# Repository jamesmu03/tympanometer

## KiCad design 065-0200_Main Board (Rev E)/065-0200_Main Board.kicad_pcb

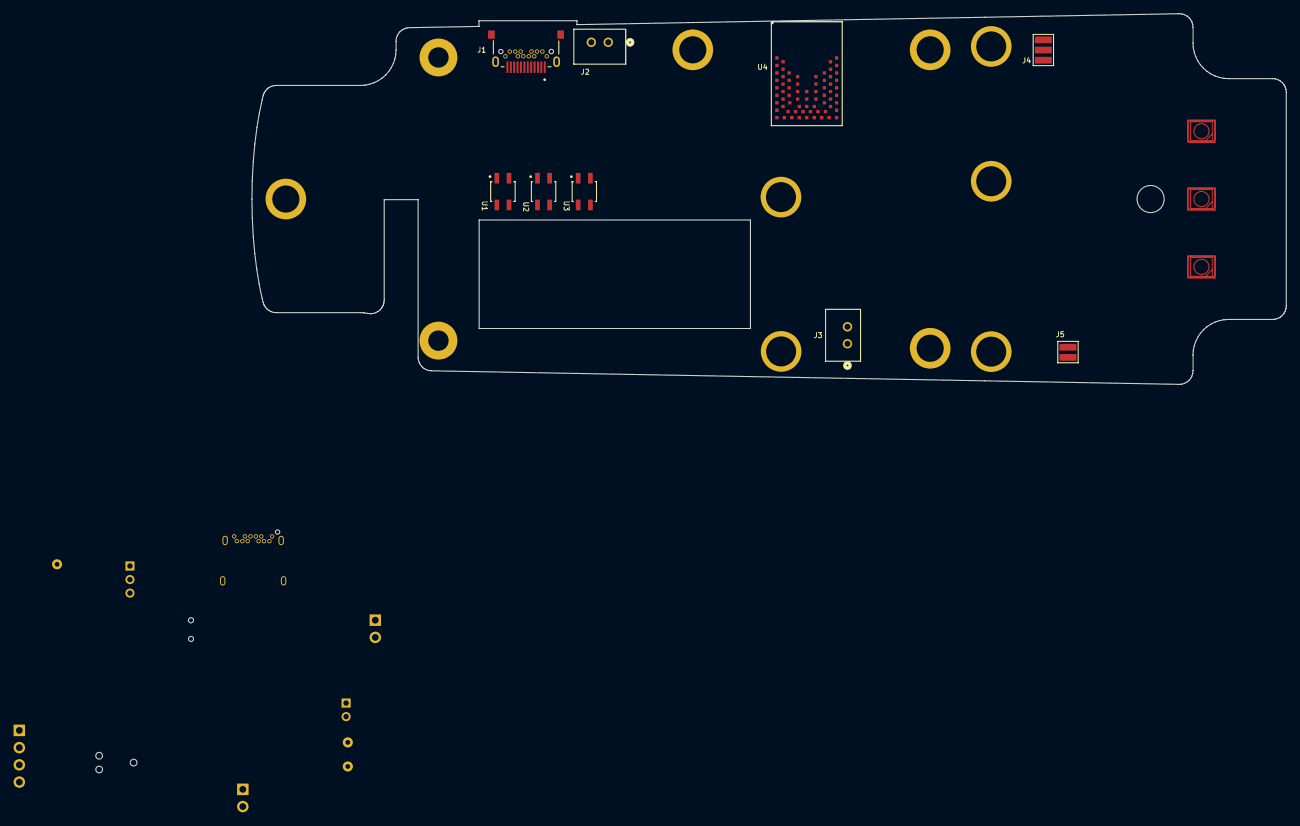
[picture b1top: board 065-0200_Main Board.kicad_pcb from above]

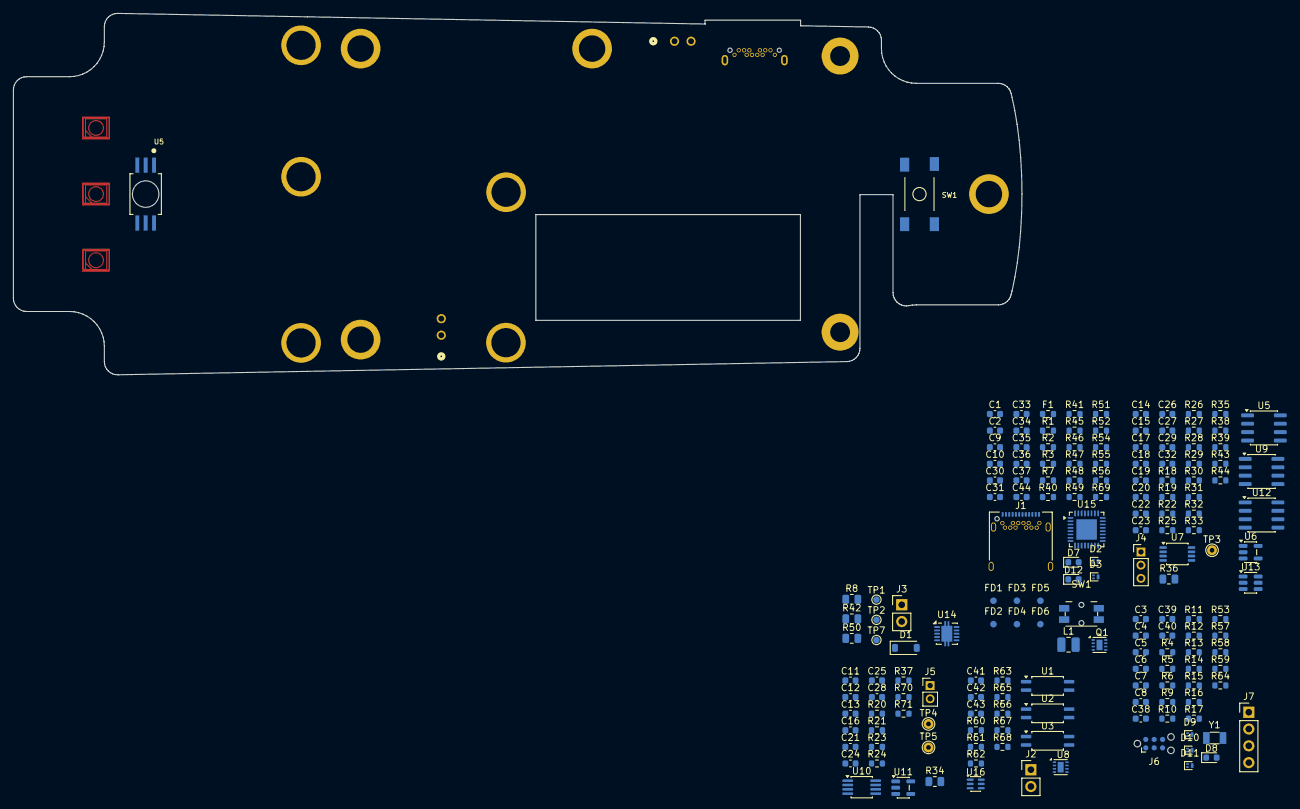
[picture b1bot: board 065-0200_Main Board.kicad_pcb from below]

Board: 2 copper layers, 152.5 x 54.6 mm, 188 parts (168 on the bottom side), 90 nets, no tracks yet.

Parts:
C1, C2, C3, C4, C5, C6, C7, C8, C9, C10, C11, C12, C13, C14, C15, C16, C17, C18, C19, C20, C21, C22, C23, C24, C25, C26, C27, C28, C29, C31, C32, C36, C37, C38, C39, C40, C41, C42, C43, C44: Cap_Ceramic; C_0603_1608Metric
C30, C33, C34: CL10A226MO7JZNC; C_0603_1608Metric
C35: C0603C102K5RACTU; C_0603_1608Metric
D1: ATV02W120B-HF; D_SOD-123
D2, D3, D9, D10, D11: D5V0H1B2LP-7B; SOT-883
D4, D5, D6: CLVBA-FKA-CAEDH8BBB7A363; LED_Cree-PLCC4_3.2x2.8mm_CCW
D7, D8, D12: APT1608ZGCK; LED_0603_1608Metric
F1: C2Q 2.5; R_0603_1608Metric
FD1, FD2, FD3, FD4, FD5, FD6: DNI; Fiducial_1mm_Mask2mm
J1: UJ32-C-H-G-H2-SMT-TR; CUI_UJ32-C-H-G-H2-SMT-TR
J1#2: UJ32-C-H-G-H2-SMT-TR; USB_C_Receptacle_Amphenol_12401548E4-2A
J2, J3: 0022035025; Molex_2P-2.50_22035025
J2#2, J3#2: 0022035025; PinHeader_1x02_P2.54mm_Vertical
J4: custom_3p_2mm; Custom_3p-2MM
J4#2: custom_3p_2mm; PinHeader_1x03_P2.00mm_Vertical
J5: custom_2p_2mm; Custom_2p-2MM
J5#2: custom_2p_2mm; PinHeader_1x02_P2.00mm_Vertical
J6: TC2030-CTX; Tag-Connect_TC2030-IDC-NL_2x03_P1.27mm_Vertical
J7: Conn_01x04_Pin; PinHeader_1x04_P2.54mm_Vertical
L1: CIGT252012LMR47MNE; L_1008_2520Metric
MH1, MH4, MH7, MH8: DNI; MH_M3_Pad
MH2, MH3, MH5, MH6, MH9, MH10, MH11: DNI; MH_M2.5_Pad
Q1: CSD25402Q3A; WSON-8-1EP_2x2mm_P0.5mm_EP0.9x1.6mm
R1, R2, R3, R4, R5, R6, R7, R9, R10, R11, R12, R13, R14, R15, R16, R17, R18, R19, R20, R21, R22, R23, R24, R25, R26, R27, R29, R30, R31, R32, R33, R35, R37, R38, R39, R40, R41, R43, R44, R45, R46, R47, R48, R49, R51, R52, R53, R54, R55, R56, R57, R58, R59, R60, R61, R62, R63, R64, R65, R66, R67, R68, R69, R70, R71: Resistor; R_0603_1608Metric
R8, R34, R36, R42, R50: Resistor; R_0805_2012Metric
R28: ERJ-3EKF6810V; R_0603_1608Metric
SW1: 3-1437565-0; Panasonic_EVQPUL_EVQPUC
SW1#2: 3-1437565-0; SW_TE_3-1437565-0
TP1, TP2, TP7: TP SMT Round 30mil; TestPoint_Pad_D1.0mm
TP3, TP4, TP5: TP TH Round 45 mil sqr, 25mil hole; TestPoint_THTPad_D1.5mm_Drill0.7mm
U1, U2, U3: QRE1113GR; SOIC180P460X187-4N
U1#2, U2#2, U3#2: QRE1113GR; SOIC-4_4.55x2.6mm_P1.27mm
U4: BM833
U5: 2SMPP03; 6SOP_2SMPP-03
U5#2: 2SMPP03; SOIC-8_3.9x4.9mm_P1.27mm
U6, U11: TLV313IDBVT; SOT-23-5
U7: INA326; TSSOP-8_3x3mm_P0.65mm
U8: DRV8837DSGR; WSON-8-1EP_2x2mm_P0.5mm_EP0.9x1.6mm
U9: LM334MX/NOPB; SOIC-8_3.9x4.9mm_P1.27mm
U10: LM4875MM/NOPB; MSOP-8_3x3mm_P0.65mm
U12: LM393DMR2G; SOIC-8_3.9x4.9mm_P1.27mm
U13: MAX9109EUT+T; SOT-23-6
U14: TPS63802DLAT; VSON-10-1EP_3x3mm_P0.5mm_EP1.65x2.4mm
U15: NPM1300-QEAA-R; QFN-32-1EP_5x5mm_P0.5mm_EP3.1x3.1mm
U16: 74LVC1G27GW,12; SOT-363_SC-70-6
Y1: 9HT10-32.768KBZF-T; Crystal_SMD_3215-2Pin_3.2x1.5mm

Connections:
+3V3: C7.2, C8.1, C14.1, C16.2, C20.1, C23.1, C24.2, C26.1, C27.2, C29.2, C32.2, C35.2, C39.1, C40.2, C41.2, C42.2, C43.2, J6.1 (VCC), J7.3, R4.2, R23.2, R29.2, R33.2, R35.1, R36.2, R42.2, R43.2, R53.2, R57.2, R58.2, R59.2, R62.2, R63.2, R65.2, R66.2, R67.2, R68.2, R69.2, U4.14, U4.28, U6.5 (+V), U7.7 (V+), U8.1 (VM), U8.8 (VCC), U9.4 (V+), U10.1 (VDD), U11.5 (+V), U12.8 (VCC), U13.6 (+V), U15.12 (VDDIO), U16.5 (VCC)
/Micro/BMD_RESET: C38.1, D9.2, J6.3 (nRESET), R59.1
/Micro/BMD_SWCLK: D10.2, J6.4 (SWCLK)
/Micro/BMD_SWDIO: D11.2, J6.2 (SWDIO)
/Micro/Back_Limit: R67.1, U1#2.3 (CT)
/Micro/Center_Limit: R65.1, U2#2.3 (CT)
/Micro/ENV_OUT: R19.2, TP3.1 (1_1), U6.1 (OUT)
/Micro/Front_Limit: R62.1, U3#2.3 (CT)
/Micro/MTR_DRV1: R61.2, U8.6 (IN1)
/Micro/MTR_DRV2: R60.2, U8.5 (IN2)
/Micro/MTR_SLEEP: R64.2, U16.3 (B)
/Micro/PRESSURE: C22.2, R31.2, U12.2 (INA-), U12.5 (INB+)
/Micro/Pressure_Error: U13.1 (OUT), U13.5 (LE), U16.6 (C)
/Micro/SCL: J7.2, R57.1, U15.14 (SCL)
/Micro/SDA: J7.1, R58.1, U15.13 (SDA)
/Micro/USB_D_N: D2.2, J1#2.A7 (DN1), J1#2.B7 (DN2)
/Micro/USB_D_P: D3.2, J1#2.A6 (DP1), J1#2.B6 (DP2)
Back_Limit: U1.3, U4.21
Center_Limit: U2.3, U4.10
Front_Limit: U3.3, U4.12
GND: C1.1, C2.1, C3.1, C4.1, C5.2, C6.1, C7.1, C8.2, C9.1, C10.1, C11.2, C12.2, C13.2, C14.2, C15.2, C16.1, C17.2, C19.2, C20.2, C22.1, C23.2, C24.1, C25.1, C26.2, C27.1, C28.2, C29.1, C30.1, C31.2, C32.1, C33.1, C34.1, C35.1, C36.1, C37.1, C38.2, C39.2, C40.1, C41.1, C42.1, C43.1, C44.1, C44.2, D1.1, D2.1, D3.1, D7.1 (K), D9.1, D10.1, D11.1, D12.1 (K), J1.A1, J1.A12, J1.B1, J1.B12, J1.SH1, J1.SH2, J1.SH3, J1.SH4, J1#2.A1 (GND), J1#2.A12 (GND), J1#2.B1 (GND), J1#2.B12 (GND), J1#2.SH (SHIELD), J3.2, J3#2.2, J4.1, J4#2.1, J6.5 (GND), J7.4, MH1.1, MH2.1, MH3.1, MH5.1, MH6.1, MH8.1, MH10.1, MH11.1, Q1.8 (G), R1.1, R2.1, R3.1, R5.1, R7.1, R18.1, R24.2, R26.1, R27.1, R39.1, R40.1, R44.1, R54.2, R55.2, R56.2, R60.1, R61.1, R64.1, R70.1, R71.1, SW1.1, SW1.2, SW1#2.1, SW1#2.2, U1.2, U1.4, U1#2.2 (C), U1#2.4 (ET), U2.2, U2.4, U2#2.2 (C), U2#2.4 (ET), U3.2, U3.4, U3#2.2 (C), U3#2.4 (ET), U4.1, U4.2, U4.3, U4.4, U4.5, U4.13, U4.15, U4.18, U4.19, U4.30, U4.45, U5.3, U5#2.3 (GND), U6.2 (-V), U7.4 (V-), U8.4 (GND), U8.9 (Therm), U10.6 (GND), U11.2 (-V), U12.4 (GND), U13.2 (GND), U14.2 (MODE), U14.3 (AGND), U14.8 (GND), U15.2 (PVSS1), U15.6 (PVSS2), U15.15 (SHPHLD), U15.16 (VSET2), U15.17 (VSET1), U15.28 (LSIN1/__VINLDO1), U15.29 (LSOUT1/__VOUTLDO1), U15.30 (LSIN2/__VINLDO2), U15.31 (LSOUT2/_VOUTLDO2), U15.33 (AVSS__EXT_PAD), U16.2 (GND)
unnamed: C11.1, C12.1, C13.1, R20.1, R21.2, R70.2, R71.2
unnamed: C18.1, C19.1, R30.1, R32.2
unnamed: D7.2 (A), R51.1
unnamed: D8.2 (A), R53.1
unnamed: D12.2 (A), R69.1
unnamed: J1#2.A5 (CC1), R3.2
unnamed: J1#2.B5 (CC2), R1.2
unnamed: J4#2.2, R32.1
unnamed: J4#2.3, R36.1
unnamed: J5#2.2, R34.2, TP4.1 (1_1)
unnamed: C9.2, C10.2, Q1.1 (S), R7.2, R8.2
unnamed: R22.1, R28.2, U9.2 (V-), U9.3 (V-), U9.6 (V-), U9.7 (V-)
unnamed: R25.1, U7.1 (R1)
unnamed: R25.2, U7.8 (R1)
unnamed: D1.2, F1.1, J1#2.A4 (VBUS), J1#2.A9 (VBUS), J1#2.B4 (VBUS), J1#2.B9 (VBUS), R2.2, TP1.1 (TP_1)
unnamed: R68.1, U1#2.1 (A)
unnamed: R66.1, U2#2.1 (A)
unnamed: R63.1, U3#2.1 (A)
unnamed: C3.2, Y1.1 (X1)
unnamed: C4.2, Y1.2 (X2)
unnamed: R5.2, R6.1
unnamed: C5.1, C6.2, R4.1
unnamed: R22.2, U5#2.5 (N-SUB), U5#2.6 (Icc)
unnamed: U5#2.1 (Vout+), U7.3 (+)
unnamed: U5#2.4 (Vout-), U7.2 (-)
unnamed: C17.1, C18.2, R27.2, R30.2, U6.3 (IN+)
unnamed: R18.2, R19.1, U6.4 (IN-)
unnamed: C15.1, R26.2, R29.1, U7.5 (R2)
unnamed: R31.1, U7.6 (VO)
unnamed: J2#2.1, U8.2 (OUT1)
unnamed: J2#2.2, U8.3 (OUT2)
unnamed: R28.1, U9.1 (R)
unnamed: C25.2, U10.7 (Bypass)
unnamed: R20.2, U10.4 (DC_VOL)
unnamed: R23.1, R24.1, U10.3 (HP_SENSE)
unnamed: C21.1, U10.2 (IN-)
unnamed: J5#2.1, TP5.1 (1_1), U10.5 (VO1)
unnamed: R34.1, U10.8 (VO2)
unnamed: C28.1, R37.2, U11.3 (IN+)
unnamed: C21.2, U11.1 (OUT), U11.4 (IN-)
unnamed: R35.2, R38.1, U12.3 (INA+)
unnamed: R33.1, U12.1 (OUTA), U12.7 (OUTB), U13.4 (IN-)
unnamed: R38.2, R39.2, U12.6 (INB-)
unnamed: R43.1, R44.2, U13.3 (IN+)
unnamed: C33.2, C34.2, R50.2, U14.1 (EN), U14.10 (VIN)
unnamed: R40.2, R41.1, U14.4 (FB)
unnamed: L1.2, U14.7 (L2)
unnamed: L1.1, U14.9 (LI)
unnamed: R45.1, U14.5 (PG)
unnamed: C30.2, C31.1, R41.2, R42.1, R45.2, U14.6 (VOUT)
unnamed: R55.1, U15.23 (CC1)
unnamed: R54.1, U15.24 (CC2)
unnamed: R46.1 (1_1), U15.7 (GPIO0)
unnamed: R47.1 (1_1), U15.8 (GPIO1)
unnamed: R48.1 (1_1), U15.9 (GPIO2)
unnamed: R49.1, U15.10 (GPIO3)
unnamed: R52.1 (1_1), U15.11 (GPIO4)
unnamed: R56.1, U15.18 (NTC)
unnamed: C37.2, U15.22 (VBUSOUT)
unnamed: U8.7 (~SLEEP), U16.4 (Y)
NetC44_1: SW1#2.3, SW1#2.4
NetD1_2: J1.A4, J1.A9, J1.B4, J1.B9
NetR22_2: U5.5, U5.6
USB_D_N: J1.A7, J1.B7, U4.68
USB_D_P: J1.A6, J1.B6, U4.67
VBUS: C1.2, C2.2, F1.2, TP2.1 (TP_1), U4.58, U15.21 (VBUS), U16.1 (A)
VBat: R8.1, U15.19 (VBAT)
VBat_IN: J3.1, J3#2.1, Q1.5 (D), Q1.6 (D), Q1.7 (D)
VSys: C36.2, R50.1, R51.2, TP7.1 (TP_1), U15.1 (VOUT), U15.4 (PVDD), U15.20 (VSYS), U15.32 (VOUT2)

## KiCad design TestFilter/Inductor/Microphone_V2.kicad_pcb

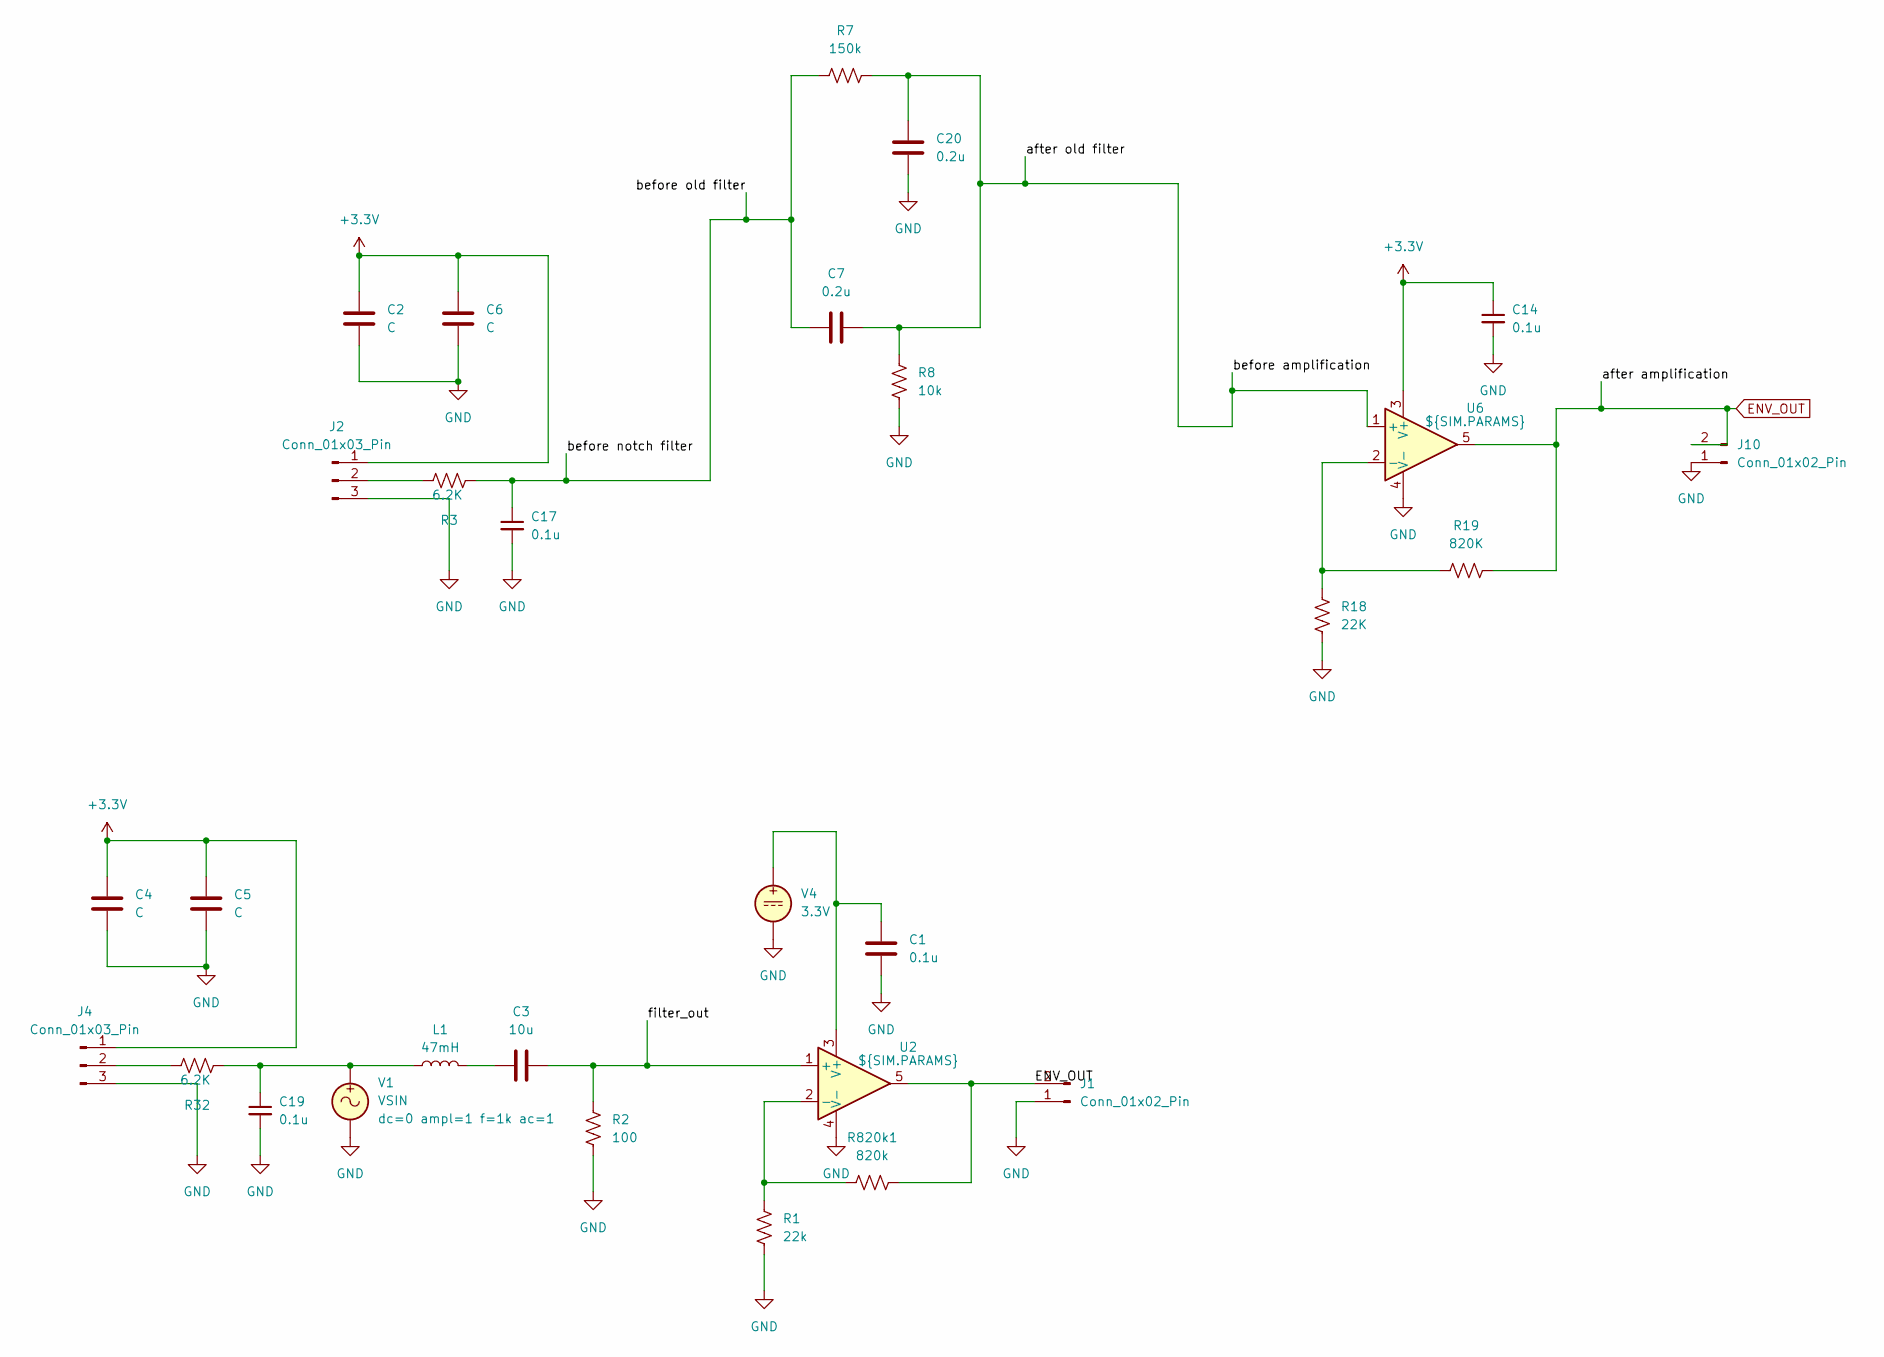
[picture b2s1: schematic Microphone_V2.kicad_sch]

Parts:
C1, C14, C17, C19: 0.1u; C_0603_1608Metric_Pad1.08x0.95mm_HandSolder
C2, C4, C5, C6: C; C_0603_1608Metric_Pad1.08x0.95mm_HandSolder
C3: 10u; C_0603_1608Metric_Pad1.08x0.95mm_HandSolder
C7, C20: 0.2u; C_0603_1608Metric_Pad1.08x0.95mm_HandSolder
J1, J10: Conn_01x02_Pin; PinHeader_1x02_P2.54mm_Vertical
J2, J4: Conn_01x03_Pin; PinHeader_1x03_P2.54mm_Vertical
L1: 47mH; L_TDK_NLV25_2.5x2.0mm
R1: 22k; R_0603_1608Metric_Pad0.98x0.95mm_HandSolder
R2: 100; R_0603_1608Metric_Pad0.98x0.95mm_HandSolder
R3, R32: 6.2K; R_0603_1608Metric_Pad0.98x0.95mm_HandSolder
R7: 150k; R_0603_1608Metric_Pad0.98x0.95mm_HandSolder
R8: 10k; R_0603_1608Metric_Pad0.98x0.95mm_HandSolder
R18: 22K; R_0603_1608Metric_Pad0.98x0.95mm_HandSolder
R19: 820K; R_0603_1608Metric_Pad0.98x0.95mm_HandSolder
R820k1: 820k; R_0603_1608Metric_Pad0.98x0.95mm_HandSolder
U2, U6: ${SIM.PARAMS}; TSOT-23-5_HandSoldering
V1: VSIN
V4: 3.3V

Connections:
+3.3V: C2.1, C4.1, C5.1, C6.1, C14.1, J2.1, J4.1, U6.3 (V+)
/after old filter: C7.2, C20.1, R7.2, R8.1, U6.1 (+)
/before notch filter: C7.1, C17.1, R3.1, R7.1
/filter_out: C3.2, R2.1, U2.1 (+)
ENV_OUT: J1.2, J10.2, R19.1, R820k1.2, U2.5, U6.5
GND: C1.2, C2.2, C4.2, C5.2, C6.2, C14.2, C17.2, C19.2, C20.2, J1.1, J2.3, J4.3, J10.1, R1.2, R2.2, R8.2, R18.2, U2.4 (V-), U6.4 (V-), V1.2, V4.2
unnamed: C3.1, L1.2
unnamed: C19.1, L1.1, R32.1, V1.1
unnamed: J2.2, R3.2
unnamed: J4.2, R32.2
unnamed: R1.1, R820k1.1, U2.2 (-)
unnamed: C1.1, U2.3 (V+), V4.1
unnamed: R18.1, R19.2, U6.2 (-)

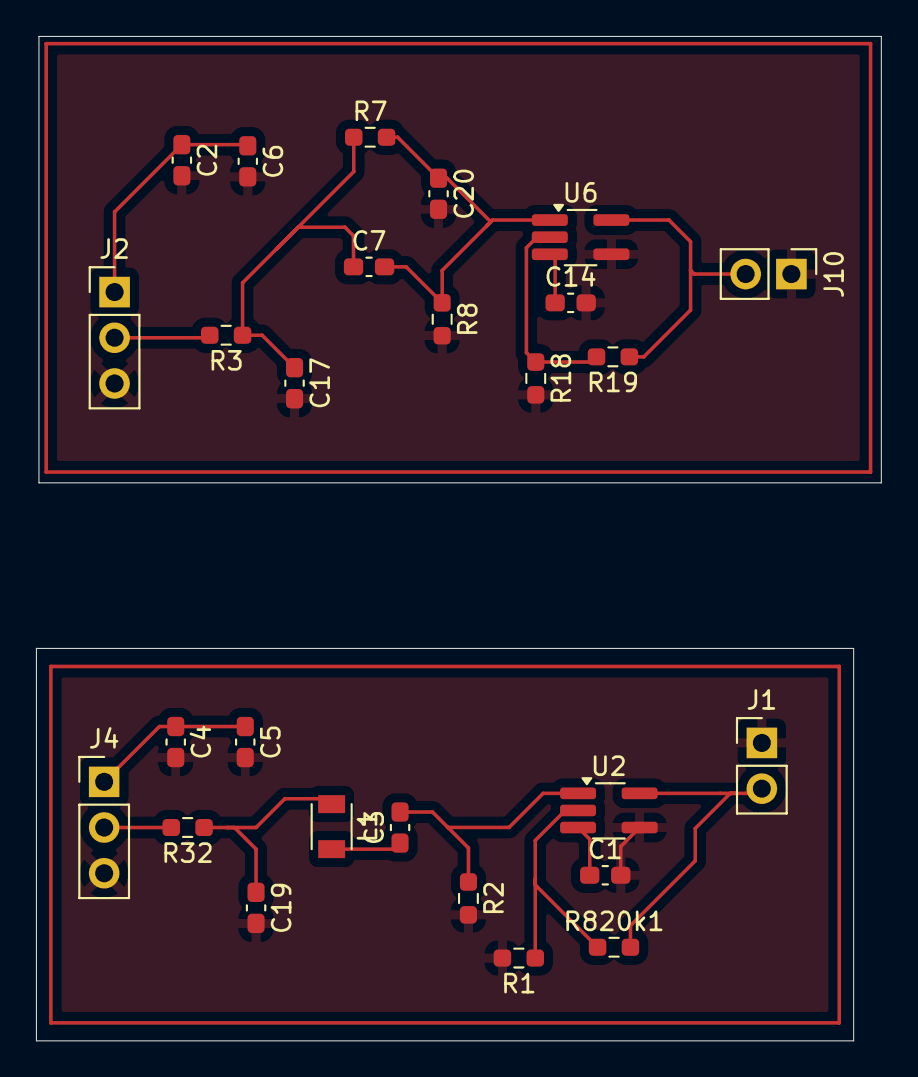
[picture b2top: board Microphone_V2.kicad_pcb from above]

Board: 2 copper layers, 46.9 x 55.8 mm, 27 parts (0 on the bottom side), 13 nets.

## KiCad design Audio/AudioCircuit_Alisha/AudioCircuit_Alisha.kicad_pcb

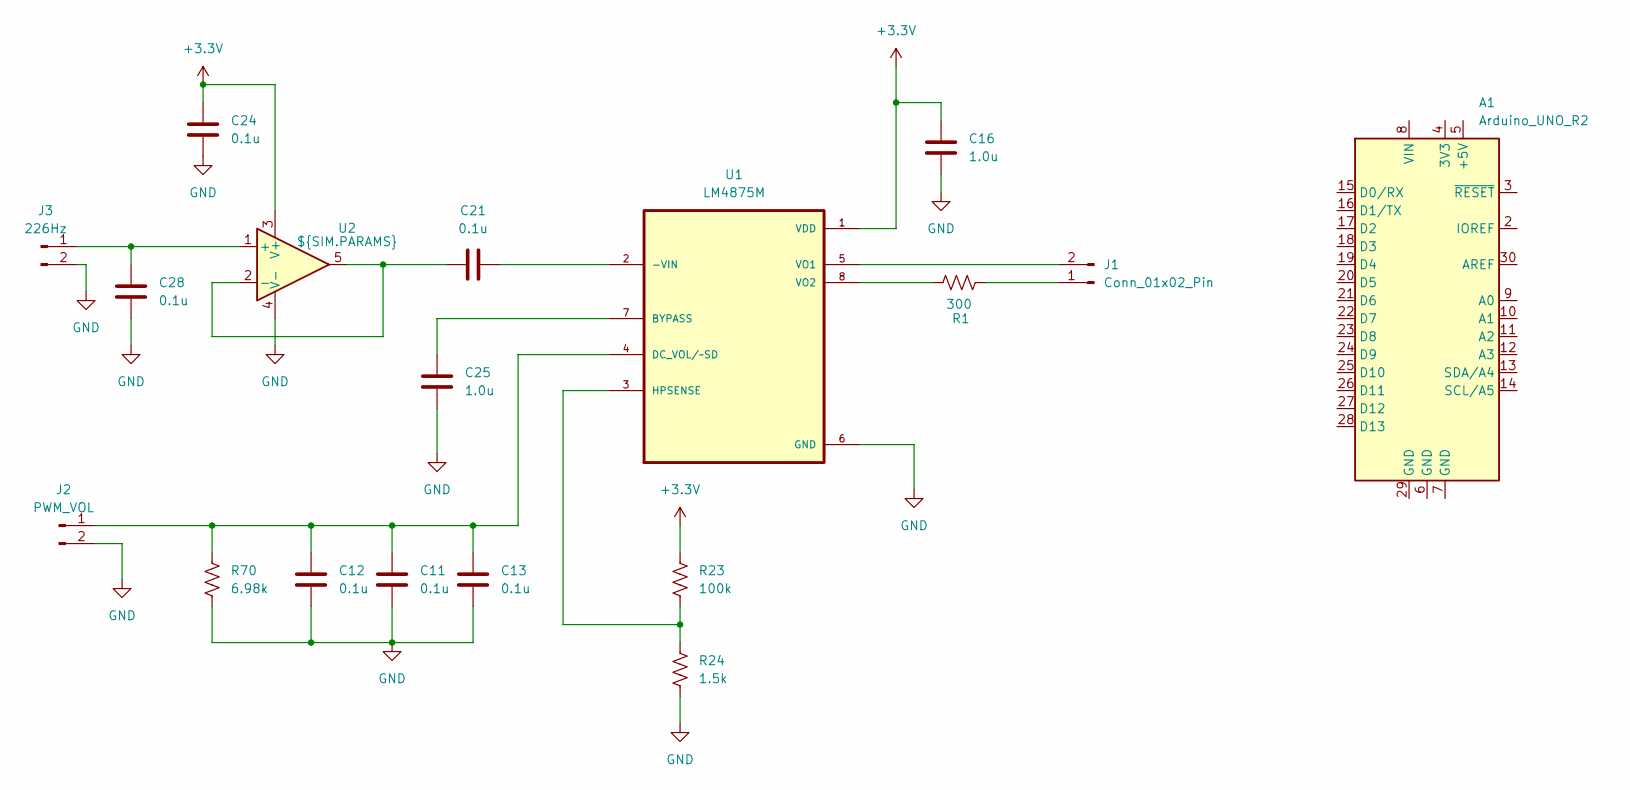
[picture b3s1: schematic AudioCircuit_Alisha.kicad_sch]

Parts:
A1: Arduino_UNO_R2
C11, C12, C13, C21, C24, C28: 0.1u
C16, C25: 1.0u
J1: Conn_01x02_Pin
J2: PWM_VOL
J3: 226Hz
R1: 300; L_Changjiang_FTC160808S
R23: 100k
R24: 1.5k
R70: 6.98k
U1: LM4875M; SOIC127P599X175-8N
U2: ${SIM.PARAMS}; DBV5_TEX-M

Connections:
+3.3V: A1.1 (NC), A1.2 (IOREF), A1.4 (3V3), C16.1, C24.1, R23.1, U1.1 (VDD), U2.3 (V+)
GND: A1.6 (GND), A1.7 (GND), A1.27 (D12), C11.2, C12.2, C13.2, C16.2, C24.2, C25.2, C28.2, J2.2, J3.2, R24.2, R70.2, U1.6 (GND), U2.4 (V-)
unnamed: J1.1, R1.2
unnamed: J1.2, U1.5 (VO1)
unnamed: C11.1, C12.1, C13.1, J2.1, R70.1, U1.4 (DC_VOL/~SD)
unnamed: C28.1, J3.1, U2.1 (+)
unnamed: C21.2, U1.2 (-VIN)
unnamed: C25.1, U1.7 (BYPASS)
unnamed: R23.2, R24.1, U1.3 (HPSENSE)
unnamed: R1.1, U1.8 (VO2)
unnamed: C21.1, U2.2 (-), U2.5

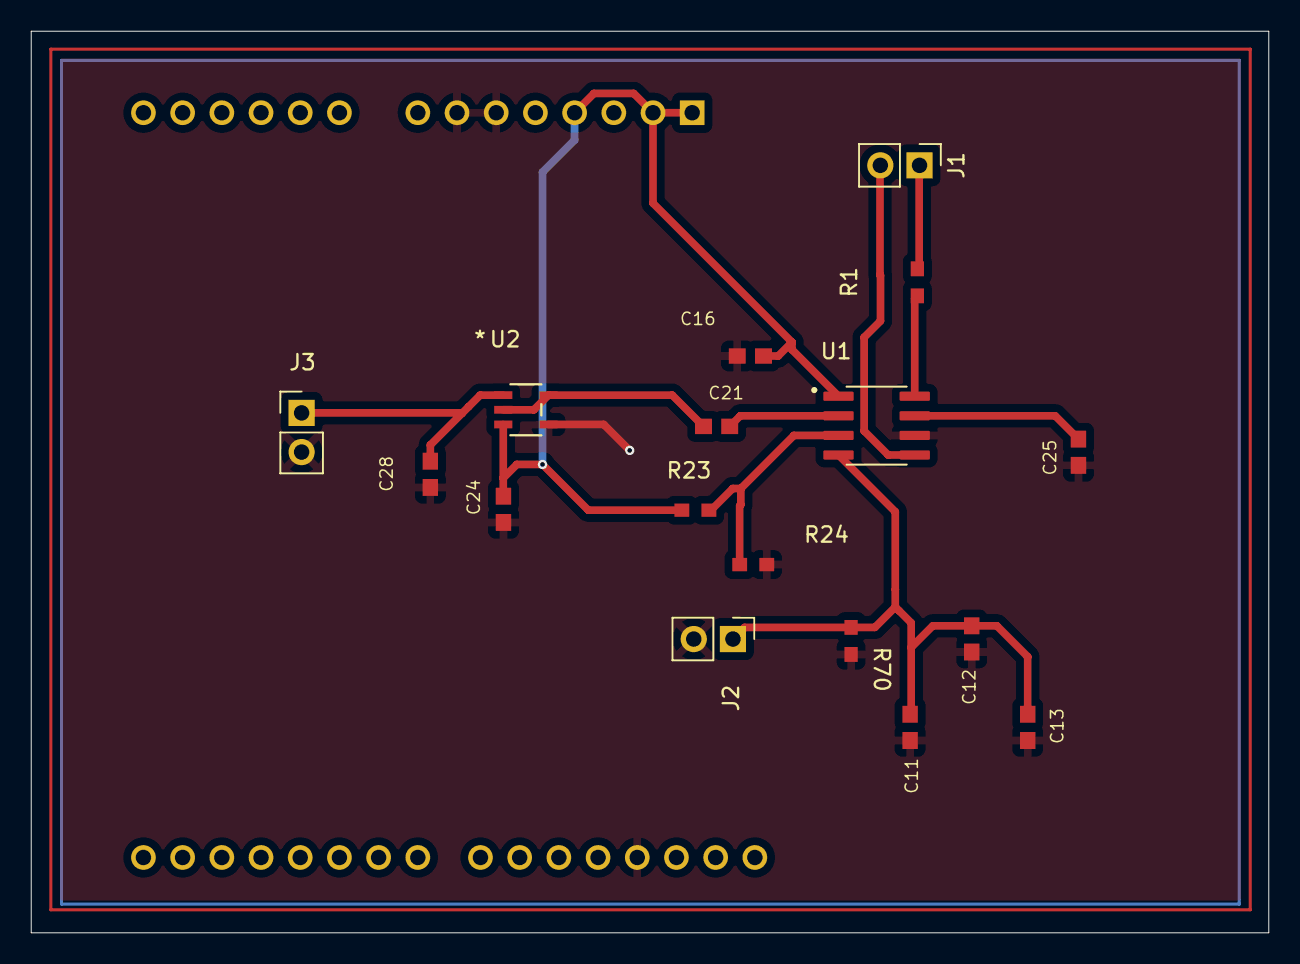
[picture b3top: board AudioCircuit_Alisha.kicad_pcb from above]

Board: 2 copper layers, 80.2 x 58.4 mm, 18 parts (1 on the bottom side), 11 nets.

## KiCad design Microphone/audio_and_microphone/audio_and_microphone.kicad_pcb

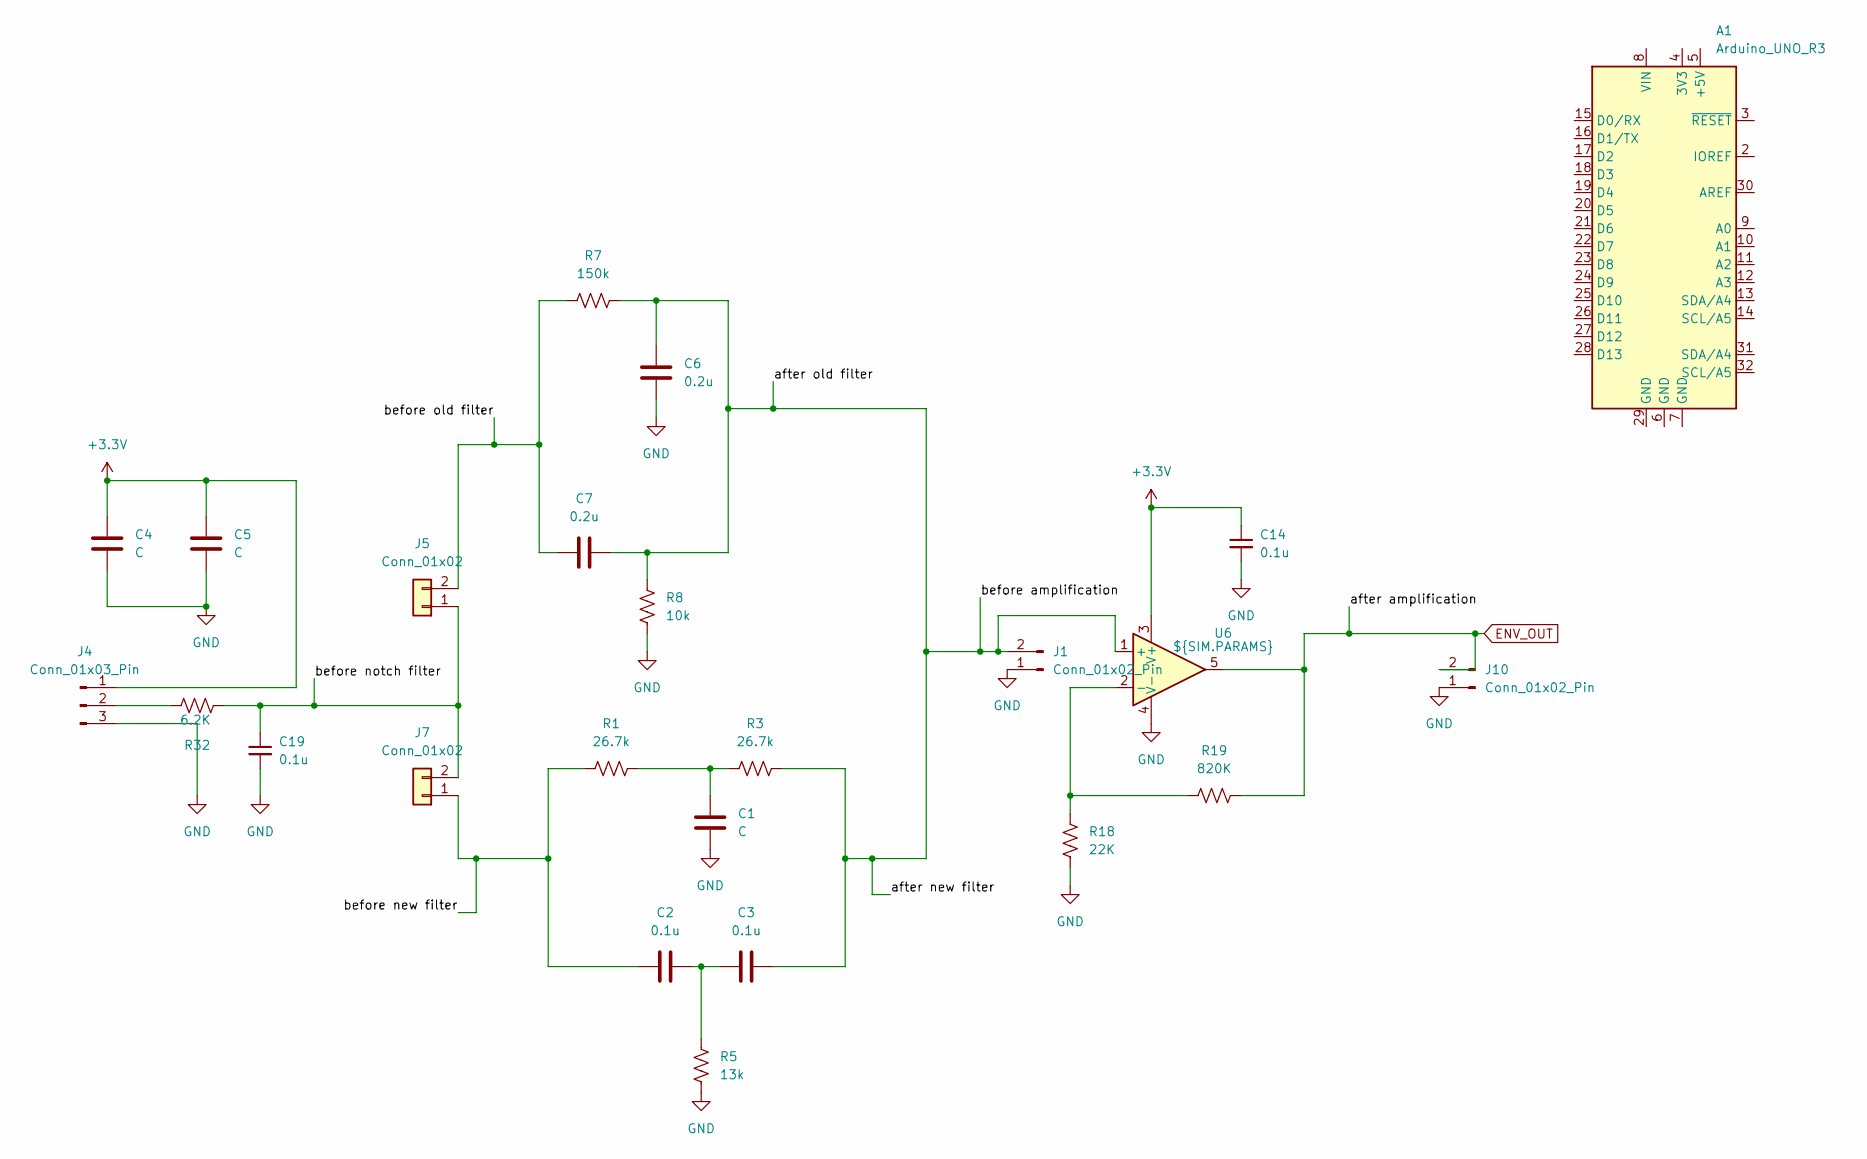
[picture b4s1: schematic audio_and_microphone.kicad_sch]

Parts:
A1: Arduino_UNO_R3
C1, C4, C5: C; C_0603_1608Metric_Pad1.08x0.95mm_HandSolder
C2, C3, C14, C19: 0.1u; C_0603_1608Metric_Pad1.08x0.95mm_HandSolder
C6, C7: 0.2u; C_0603_1608Metric_Pad1.08x0.95mm_HandSolder
J1, J10: Conn_01x02_Pin; PinHeader_1x02_P2.54mm_Vertical
J4: Conn_01x03_Pin; PinHeader_1x03_P2.54mm_Vertical
J5, J7: Conn_01x02; PinHeader_1x02_P2.54mm_Vertical
R1, R3: 26.7k; R_0603_1608Metric_Pad0.98x0.95mm_HandSolder
R5: 13k; R_0603_1608Metric_Pad0.98x0.95mm_HandSolder
R7: 150k; R_0603_1608Metric_Pad0.98x0.95mm_HandSolder
R8: 10k; R_0603_1608Metric_Pad0.98x0.95mm_HandSolder
R18: 22K; R_0603_1608Metric_Pad0.98x0.95mm_HandSolder
R19: 820K; R_0603_1608Metric_Pad0.98x0.95mm_HandSolder
R32: 6.2K; R_0603_1608Metric_Pad0.98x0.95mm_HandSolder
U6: ${SIM.PARAMS}; TSOT-23-5_HandSoldering

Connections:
+3.3V: A1.2 (IOREF), C4.1, C5.1, C14.1, J4.1, U6.3 (V+)
/after new filter: C3.2, C6.1, C7.2, J1.2, R3.2, R7.2, R8.1, U6.1 (+)
/before new filter: C2.1, J7.1, R1.1
/before notch filter: C19.1, J5.1, J7.2, R32.1
/before old filter: C7.1, J5.2, R7.1
ENV_OUT: J10.2, R19.1, U6.5
GND: A1.6 (GND), A1.7 (GND), A1.29 (GND), C1.2, C4.2, C5.2, C6.2, C14.2, C19.2, J1.1, J4.3, J10.1, R5.2, R8.2, R18.2, U6.4 (V-)
unnamed: C1.1, R1.2, R3.1
unnamed: C2.2, C3.1, R5.1
unnamed: J4.2, R32.2
unnamed: R18.1, R19.2, U6.2 (-)

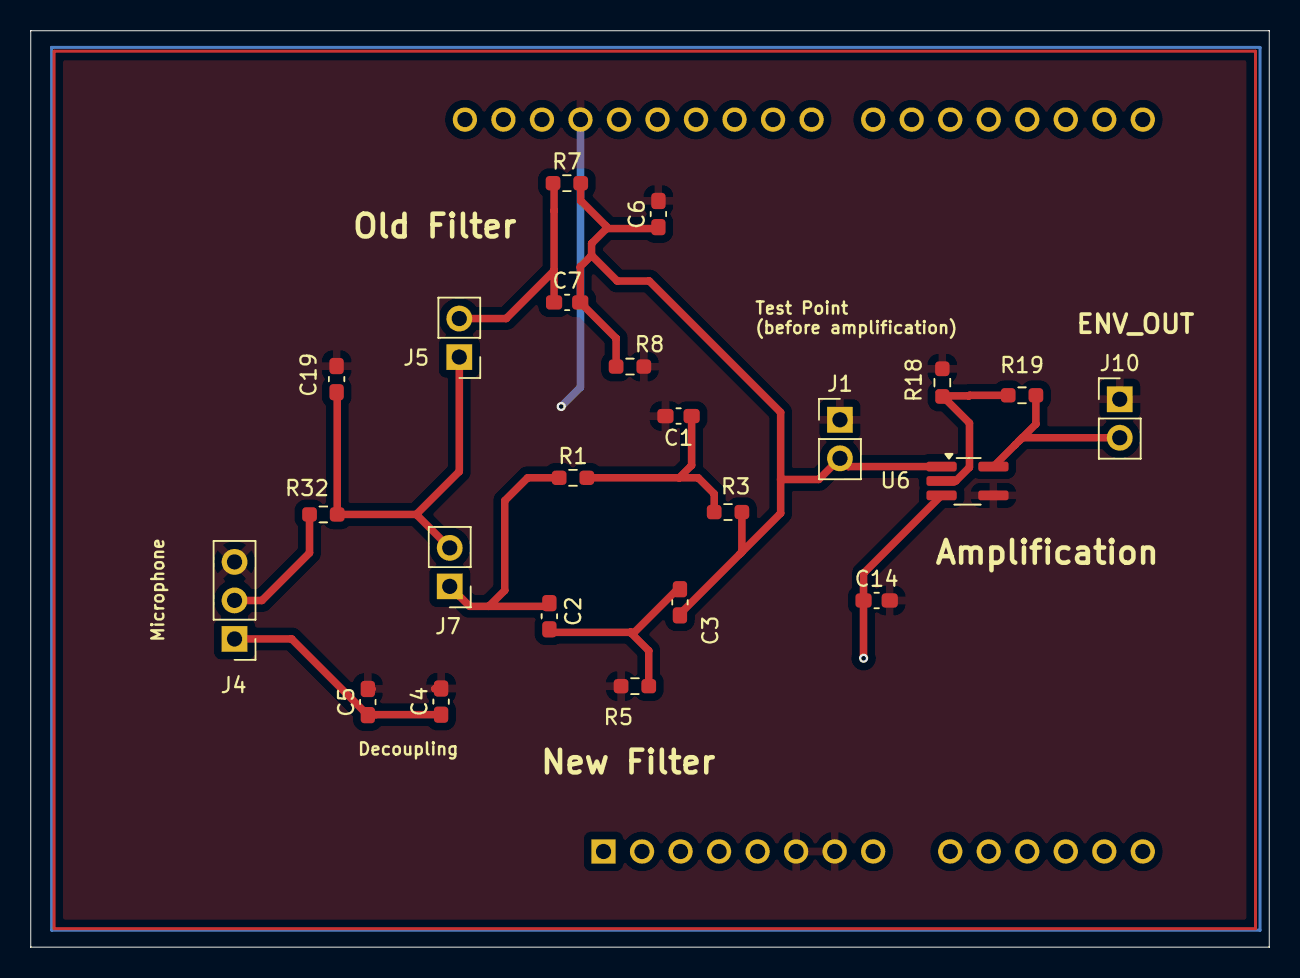
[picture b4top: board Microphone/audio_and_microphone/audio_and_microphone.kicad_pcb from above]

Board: 2 copper layers, 81.7 x 60.4 mm, 24 parts (1 on the bottom side), 11 nets.

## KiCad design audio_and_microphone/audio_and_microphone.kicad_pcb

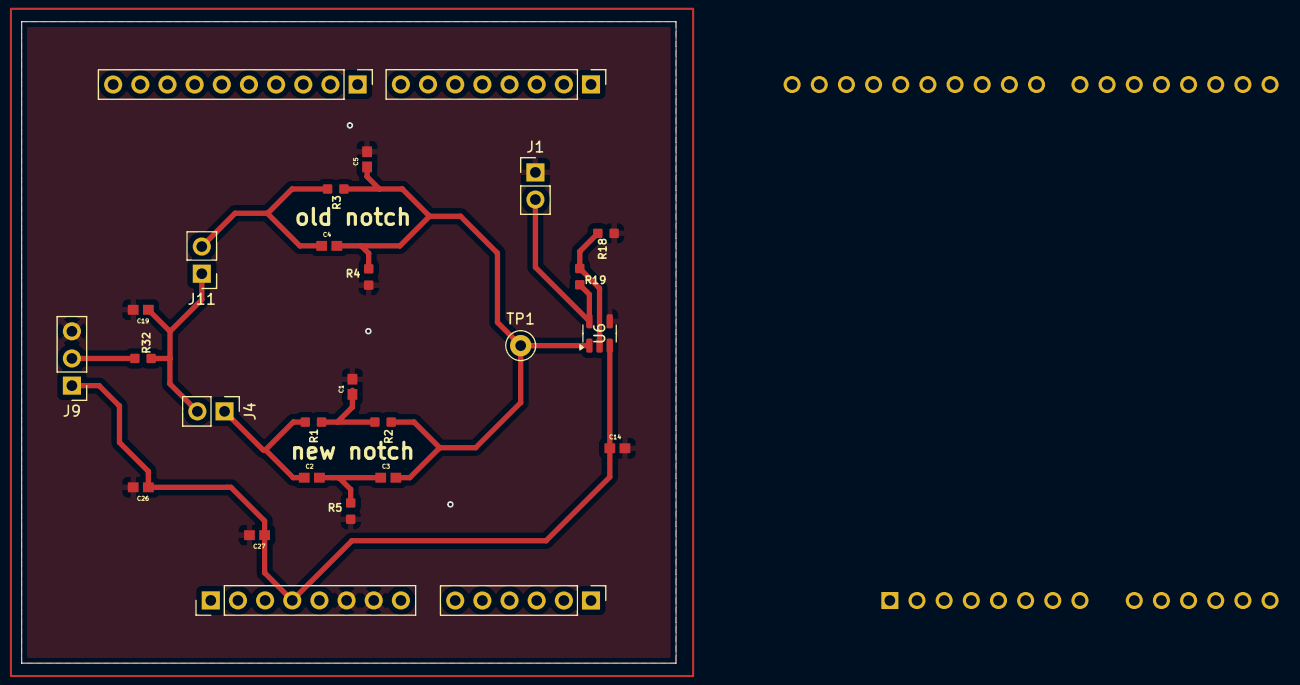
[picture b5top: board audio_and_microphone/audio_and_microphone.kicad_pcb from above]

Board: 2 copper layers, 61.2 x 60.0 mm, 28 parts (1 on the bottom side), 11 nets.

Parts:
A1: Arduino_UNO_R3
C1: 0.2u; CAPC1608X90N
C2, C3, C4, C5, C14, C19, C26: 0.1u; CAPC1608X90N
C27: 1.0u; CAPC1608X90N
J1, J4, J11: Conn_01x02; PinHeader_1x02_P2.54mm_Vertical
J5: Conn_01x10_MountingPin; PinHeader_1x10_P2.54mm_Vertical
J6, J7: Conn_01x08_MountingPin; PinHeader_1x08_P2.54mm_Vertical
J8: Conn_01x06_MountingPin; PinHeader_1x06_P2.54mm_Vertical
J9: Conn_01x03_Pin; PinHeader_1x03_P2.54mm_Vertical
R1, R2: 26.7k; R0603
R3: 150k; R0603
R4: 10k; R0603
R5: 13k; R0603
R18: 22K; R0603
R19: 820K; R0603
R32: 6.2K; R0603
TP1: TestPoint; TestPoint_Keystone_5000-5004_Miniature
U6: SOT-23-5

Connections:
+3V3: C14.1, C26.1, C27.1, J7.4, J9.1, U6.3 (V+)
/ENV_OUT: J1.2, R19.1, U6.5
/low_pass_filter: C19.1, J4.2, J11.1, R32.1
/new_notch: C3.2, C4.2, C5.1, R2.2, R3.2, R4.1, TP1.1, U6.1 (+)
GND: C1.2, C5.2, C14.2, C19.2, C26.2, C27.2, J1.1, J7.6, J7.7, J9.3, R4.2, R5.2, R18.2, U6.4 (V-)
unnamed: C1.1, R1.2, R2.1
unnamed: C2.2, C3.1, R5.1
unnamed: C2.1, J4.1, R1.1
unnamed: C4.1, J11.2, R3.1
unnamed: R18.1, R19.2, U6.2 (-)
input: J9.2, R32.2

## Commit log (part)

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2026-02-09 pulled from main branch audio and microphone circuit
2026-02-09 deleted audio circuit from microhpone
2026-02-11 assigned footprints and imported SMT designs to pcb layout
2026-02-11 updated footprints and pcb layout without 3.3 V connection
2026-02-11 improved pcb space layout
2026-02-11 created inital pcb layout
2026-02-18 excluded voltage sources from board and replaced with connectors
2026-02-18 pcb update with pin connectors
2026-02-18 updated pcb with components and locked pin holders NON THRU
2026-02-18 pcb with vertical and horizontal male header pins lined up with arduino size
2026-02-23 old and new notch filter on schematic and pcb with switch connectors
2026-02-23 updated pcb board with switch mechanisms for old vs new filters and tht pin holes
2026-02-25 completed microphone circuit and updated the parts to match altium, ready for mill
2026-02-26 updated and imported footprints to match altium
2026-02-26 fixed ground island in pcb
2026-02-27 added ground vias to bottom copper layer to fix islands
2026-02-27 updated pcb with two sides and back side with voltage
2026-02-27 changed trace size and 90 degree angles
2026-03-02 updated pcb to be cleaner with net labels and no redundancy
2026-03-02 labeled schematic and fixed track widths in pcb. passed drc
2026-03-02 added labels on pcb
2026-03-02 updated track properties, deleted switch, and fixed design rules errors
2026-03-02 updated autosave changes
2026-03-04 added additional test point and fixed pcb words to be silkscreen
2026-03-04 moved components all to one side and added silkscreen text
2026-03-04 added additional testing point and more silkscreen texts
2026-03-07 created audio circuit
2026-03-07 audio pcb added footprints, arduino board, and copper
2026-03-07 audio circuit saved updates
2026-03-24 updating folders and pcb unsaved changes 3/24/26
2026-04-03 Deleted unused files on branch and renaming files. Created new bandpass filter to attenuate 226 Hz
2026-04-05 init blank branch for altium
2026-04-06 added different filters to test
2026-04-06 adjusted to include full schematic sheets
2026-04-20 improved multiple feedback filter
2026-04-20 chore: untrack archive zips and KiCad lock/autosave files
    Add *.zip, ~*.lck, and #auto_saved_files# to .gitignore and remove
    existing tracked instances from the index. Files remain on disk.
2026-04-20 update MultipleFeedbackActive schematic; add MFB_NegativeFeedback_BufferInFront variant
2026-04-20 pushing git organization
